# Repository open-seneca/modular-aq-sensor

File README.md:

| PCB version | Code version | Name | Pilot date | Lifecycle |
| :---: | :---: | :---: | :---: | :---: |
| v3 | v10 | Europe 21 | current | in production |
| v2 | v8/v9 | Kenya 20 | Mar-20 | in stock |
| v1 | v7 | Argentina 19 | May-19 | discontinued |
| v0 | v4 | CamBike sensor | Aug-18 | discontinued |

Please also refer to our current, smaller, and all-integrated air quality sensor kit which is also open-source on Github: 
https://github.com/open-seneca/integrated-aq-sensor

If you already have a sensor and want to upload and visualise your data you can create an account here:
http://app.open-seneca.org

If you have built your kit and want to flash the code to the Black Pill board, here is how:

a) Wiring and onboard jumpers:
- RX on the USB2TTL adapter to PA9, TX to PA10, GND to G, 3.3V to V3
- jumper B0+ to center pin, B1- to center pin

b) To flash the code:
- install Arduino Due in IDE board manager
- put Arduino_STM32 library (from the "hardware" folder in this repo) in "My Documents/Arduino/hardware" (Note: if the hardware folder doesn't exist you will need to create it)
- do the same for the content of the "library" folder in this repo
- start Arduino IDE and open the latest bp_vX from this repository
- under "Tools -> Board" select "Generic STM32F103C series"
- under "Tools -> Upload method" select Serial
- press reset button on the Black Pill to enter its flash mode
- click "Upload" to flash your code

c) To execute the code:
- after flashing code should run
- plug both header pins on low (B1- should be low already if your followed the steps correctly, move other jumper to B0-)
- the board will now keep its flash memory, every reset will restart execution

We are an open-source project, please feel free to extend and improve our code, just post a commit!

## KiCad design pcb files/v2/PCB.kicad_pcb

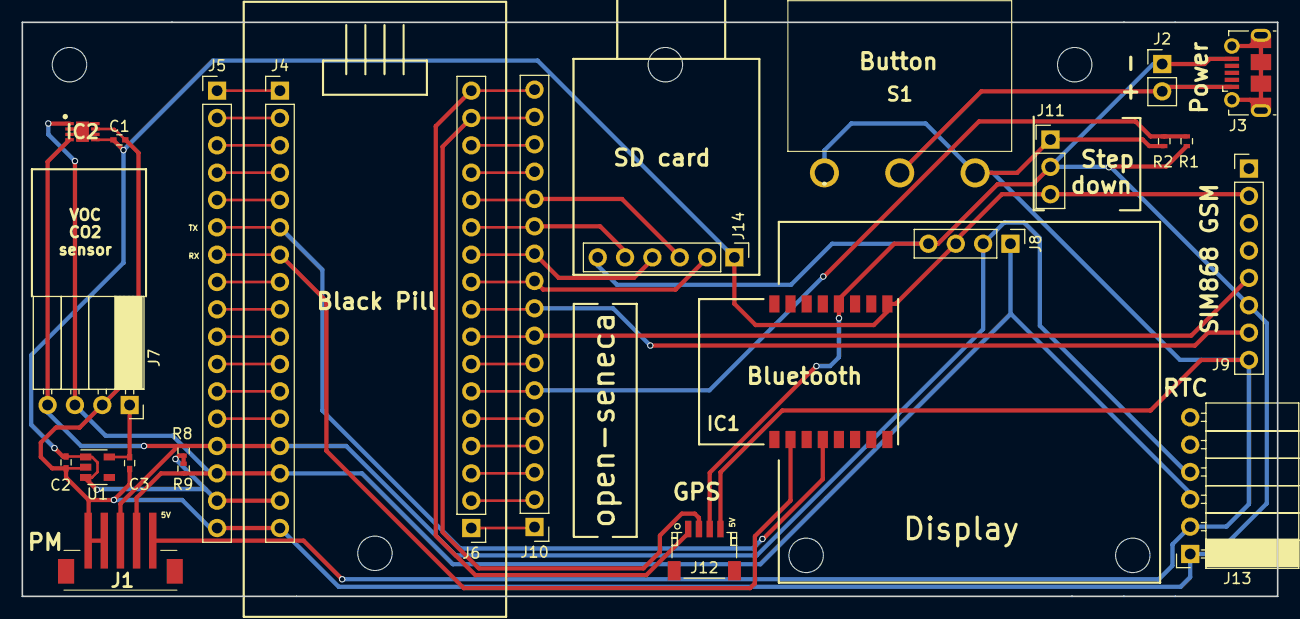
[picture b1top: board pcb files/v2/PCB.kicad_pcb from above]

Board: 2 copper layers, 116.6 x 53.3 mm, 31 parts (0 on the bottom side), 37 nets.

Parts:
C1: 100 nF; C_0402
C2, C3: 1 uF; C_0402
IC1: HM-11; HM-11-MODULE
IC2: SHT31-DIS-B; SON50P250X250X90-9N-D
J1: Conn_01x05; B5B-ZR-SM4-TF
J2: Conn_01x02; Pin_Header_Straight_1x02_Pitch2.54mm
J3: USB_OTG; USB_Micro-B_Molex-105017-0001
J4, J5, J6, J10: Conn_01x17; Socket_Strip_Straight_1x17_Pitch2.54mm
J7: Conn_01x04; Socket_Strip_Angled_1x04_Pitch2.54mm
J8: Conn_01x04; Socket_Strip_Straight_1x04_Pitch2.54mm
J9: Conn_01x08; Socket_Strip_Straight_1x08_Pitch2.54mm
J11: Conn_01x03; Socket_Strip_Straight_1x03_Pitch2.54mm
J12: Conn_01x04; JST_SH_SM04B-SRSS-TB_04x1.00mm_Angled
J13: Conn_01x06; Socket_Strip_Angled_1x06_Pitch2.54mm
J14: Conn_01x06; Socket_Strip_Straight_1x06_Pitch2.54mm
MK1, MK2, MK3, MK4, MK5, MK6: Mounting_Hole; MountingHole_3.2mm_M3
R1, R2, R8, R9: 4.7k; R_0402
S1: CWSA11AAN1H
U1: TLV70218_SOT23-5; SOT-23-5

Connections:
+3V3: C1.1, C2.1, IC1.9, IC2.5, J4.16, J5.16, J8.3, J9.2, J11.3, J14.1, R8.2, R9.2, U1.1, U1.3
+5V: J1.1, J9.8, J11.1, J12.4, J13.2, R2.1, S1.1, S1.3
/BT_RX: IC1.4, J4.6, J5.6
/BT_TX: IC1.2, J4.7, J5.7
/Bat: J6.6, J10.6, R1.1, R2.2
/Blue: J6.7, J10.7
/CStoSD: J6.10, J10.10, J14.2
/GPS_RX: J6.16, J10.16, J12.2
/GPS_TX: J6.17, J10.17, J12.1
/GSM_RX: J6.8, J9.5, J10.8
/GSM_TX: J6.9, J9.7, J10.9
/Green: J6.14, J10.14
/MISOtoSD: J6.12, J10.12, J14.5
/MOSItoSD: J6.13, J10.13, J14.3
/Red: J6.15, J10.15
/SCKtoSD: J6.11, J10.11, J14.4
/SCL: IC2.4, J1.3, J4.14, J5.14, J7.4, J8.2, J13.4, R8.1
/SDA: IC2.1, J1.2, J4.15, J5.15, J7.3, J8.1, J13.3, R9.1
GND: C1.2, C2.2, C3.2, IC1.12, IC2.2, IC2.7, IC2.8, IC2.9, J1.4, J1.5, J2.1, J3.5, J4.17, J5.17, J7.2, J8.4, J9.6, J11.2, J12.3, J13.1, J14.6, R1.2, U1.2
unnamed: C3.1, J7.1, U1.5
unnamed: J2.2, J3.1, S1.2
unnamed: J4.1, J5.1
unnamed: J4.2, J5.2
unnamed: J4.3, J5.3
unnamed: J4.4, J5.4
unnamed: J4.5, J5.5
unnamed: J4.8, J5.8
unnamed: J4.9, J5.9
unnamed: J4.10, J5.10
unnamed: J4.11, J5.11
unnamed: J4.12, J5.12
unnamed: J4.13, J5.13
unnamed: J6.1, J10.1
unnamed: J6.2, J10.2
unnamed: J6.3, J10.3
unnamed: J6.4, J10.4
unnamed: J6.5, J10.5

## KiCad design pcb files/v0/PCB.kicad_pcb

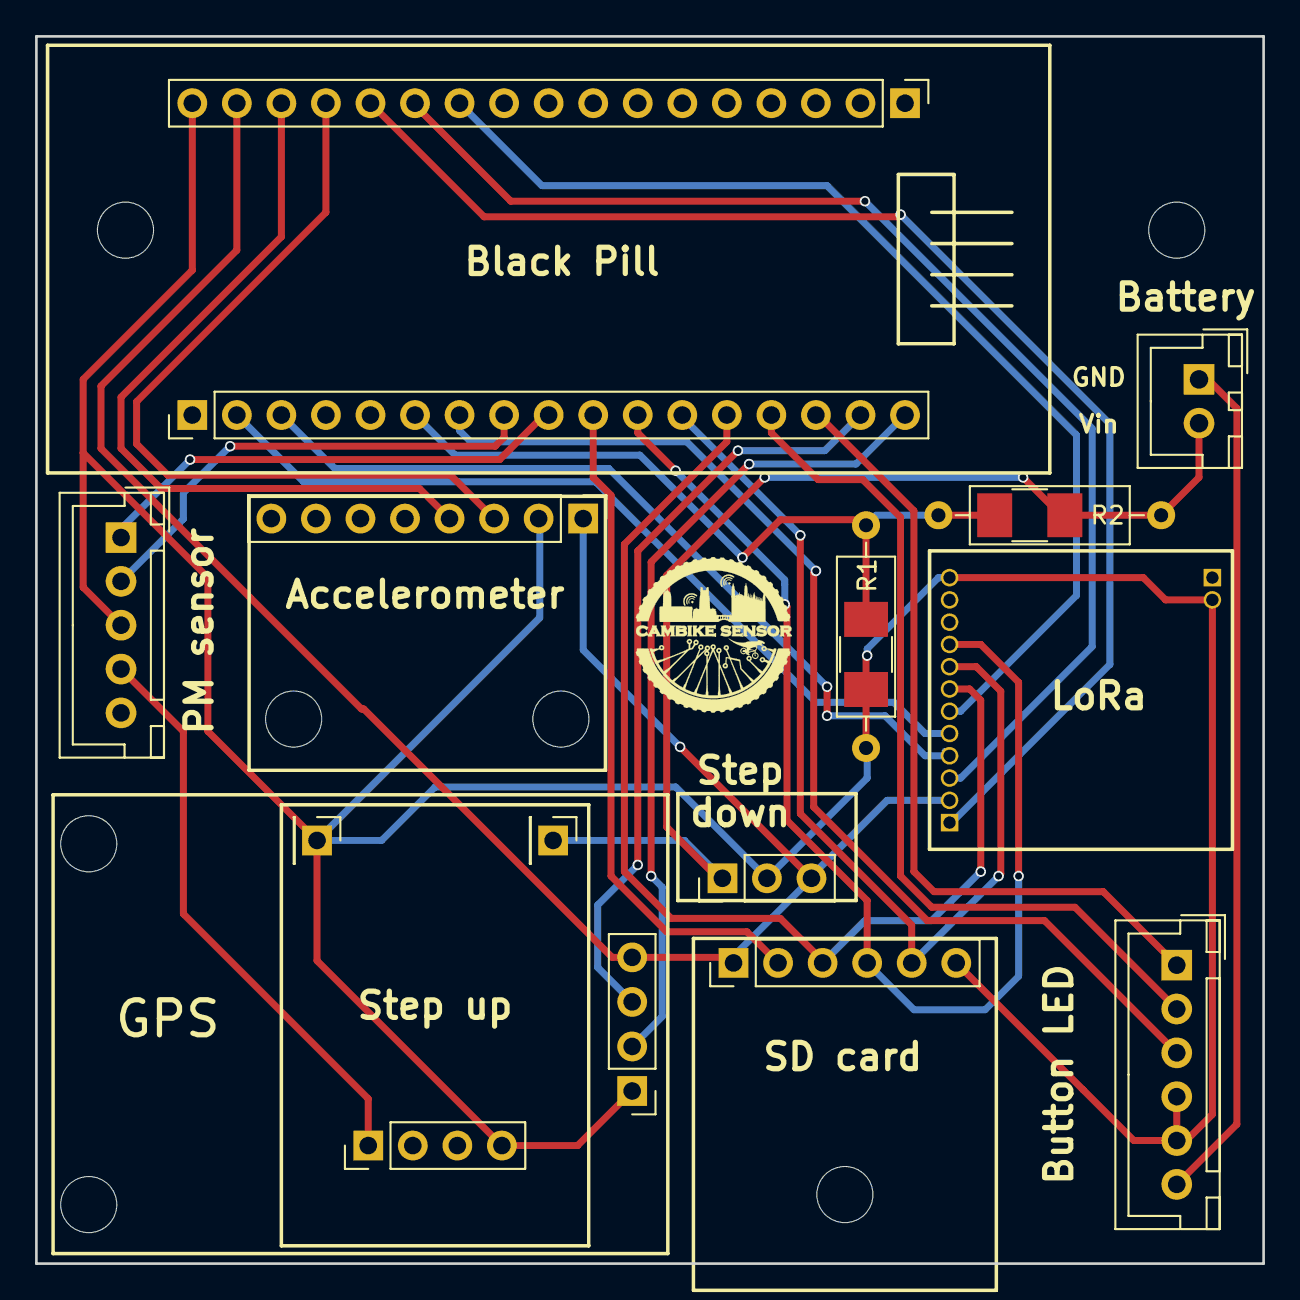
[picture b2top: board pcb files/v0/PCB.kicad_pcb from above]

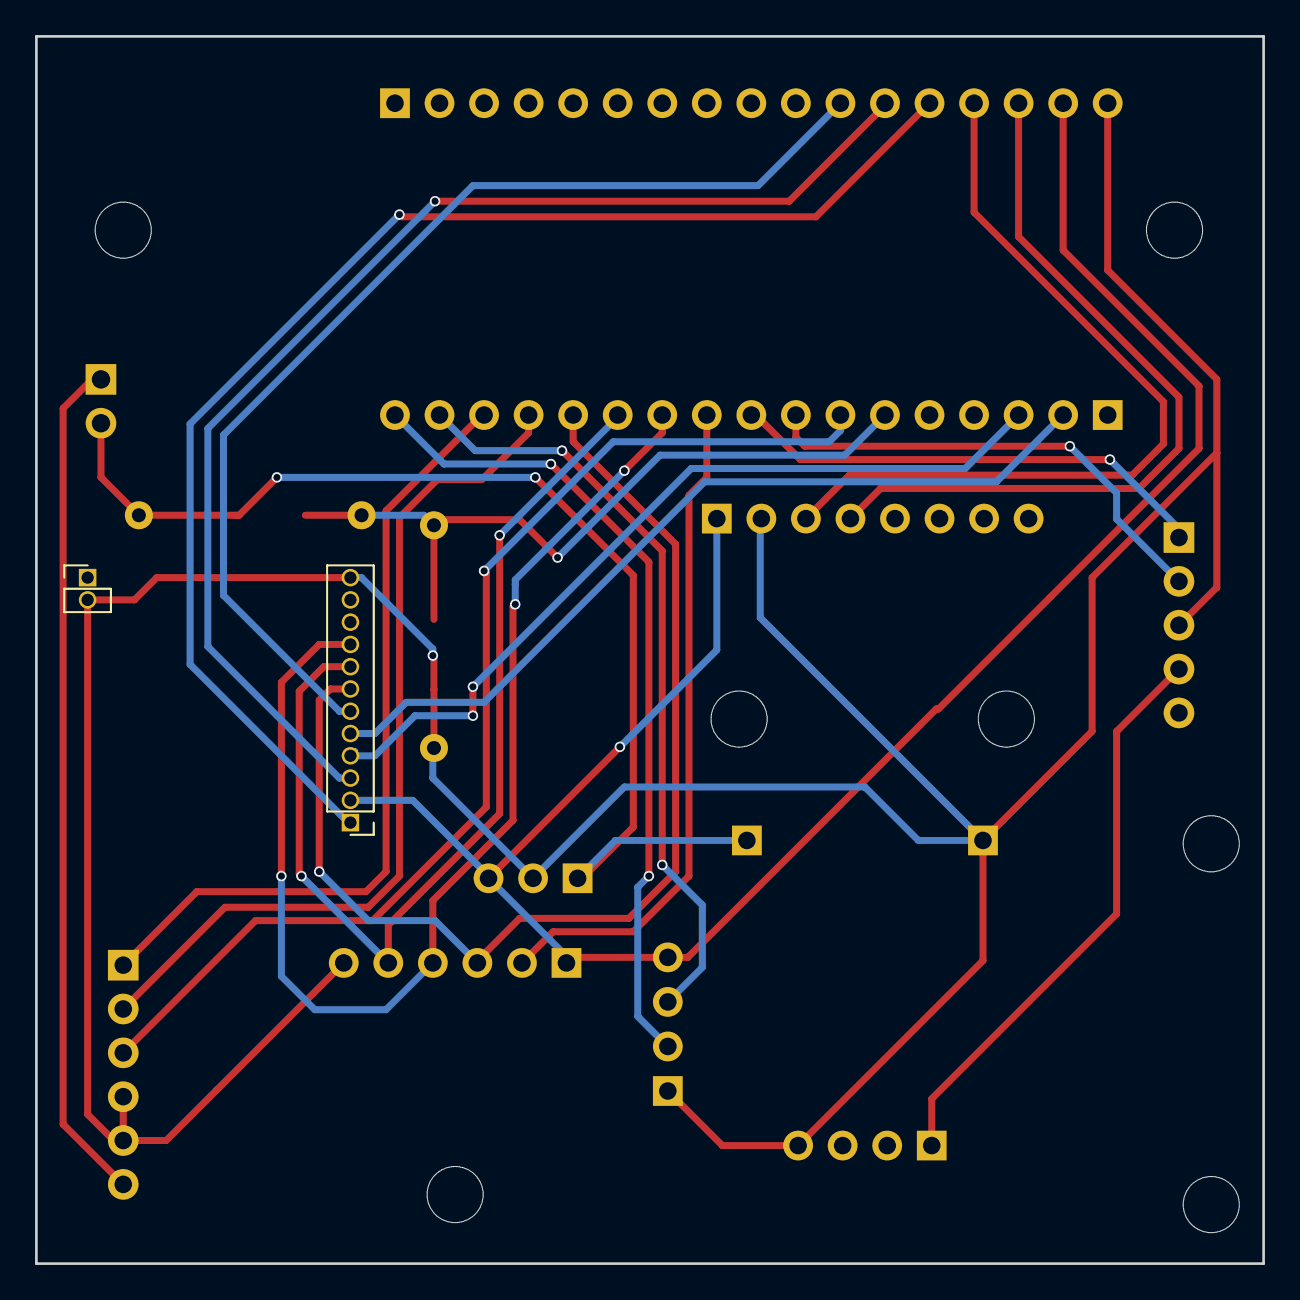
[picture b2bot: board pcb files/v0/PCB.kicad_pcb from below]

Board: 2 copper layers, 70.0 x 70.0 mm, 25 parts (2 on the bottom side), 24 nets.

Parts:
J1: Conn_01x08; Socket_Strip_Straight_1x08_Pitch2.54mm
J2: Conn_01x02; Socket_Strip_Straight_1x02_Pitch1.27mm
J3: Conn_01x12; Socket_Strip_Straight_1x12_Pitch1.27mm
J4: Conn_01x02; JST_XH_B02B-XH-A_02x2.50mm_Straight
J5, J10: Conn_01x17; Socket_Strip_Straight_1x17_Pitch2.54mm
J6, J7: Conn_01x01; Socket_Strip_Straight_1x01_Pitch2.54mm
J8: Conn_01x06; JST_XH_B06B-XH-A_06x2.50mm_Straight
J9, J12: Conn_01x04; Socket_Strip_Straight_1x04_Pitch2.54mm
J11: Conn_01x03; Socket_Strip_Straight_1x03_Pitch2.54mm
J13: Conn_01x05; JST_XH_B05B-XH-A_05x2.50mm_Straight
J14: Conn_01x06; Socket_Strip_Straight_1x06_Pitch2.54mm
MK1, MK2, MK3, MK4, MK5, MK6, MK7: Mounting_Hole; MountingHole_3.2mm_M3
R1, R2: 22k; R_1210_HandSoldering
R3, R4: 22k; R_Axial_DIN0309_L9.0mm_D3.2mm_P12.70mm_Horizontal

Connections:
+3V3: J1.1, J3.2, J5.16, J11.3, J12.4, J14.1
+5V: J9.1, J13.4
/Bat: J10.6, R1.1, R2.2, R3.1, R4.2
/Blue: J8.3, J10.7
/CS: J3.6, J5.11
/CStoSD: J10.10, J14.2
/DI0: J3.3, J5.12
/DI01: J3.4, J10.3
/DI02: J3.5, J10.2
/GPS_RX: J10.16, J12.3
/GPS_TX: J10.17, J12.2
/Green: J8.2, J10.14
/MISOtoSD: J3.8, J10.12, J14.5
/MOSItoSD: J3.7, J10.13, J14.3
/NO: J4.1, J8.6
/RESET: J3.1, J5.13
/RXtoSDS: J10.8, J13.2
/Red: J8.1, J10.15
/SCKtoSD: J3.9, J10.11, J14.4
/SCL: J1.3, J5.14
/SDA: J1.4, J5.15
/TXtoSDS: J10.9, J13.1
/Vin: J4.2, J6.1, J11.1, R2.1, R4.1
GND: J1.2, J2.2, J3.12, J5.17, J7.1, J8.4, J8.5, J9.4, J11.2, J12.1, J13.3, J14.6, R1.2, R3.2

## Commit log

2018-07-30 Readme updated
2018-07-30 Clean up
2018-08-01 Minor update
2018-08-02 Added battery status light
2018-08-15 Improved explanations
2018-08-15 Improvements
2018-08-27 PCB included
2018-08-30 Added laser cut case design file
2018-09-05 Cleanup and added casing files
2018-09-26 Updated assembly guide
2018-12-15 Added RGB LED button support
2019-03-16 Added bp_v5 (Kenya prototype)
2019-04-22 Code cleanup for ARG
2019-04-27 ARG update
2019-04-28 Fixed issues with v6
    GSM now more reliable
    CSV column order changed
2019-05-14 Updated documentation
2019-05-27 Added airflow model and PCB design
2019-08-12 v7 added
2019-09-09 Added v8 with VOC sensor support
2019-09-09 Fixing issue for VOC not plugged
2019-09-19 Gerber file v8
2019-09-19 Deleted unnecessary files
2019-09-19 Added PCB and pinout v8
2019-11-23 Added files for Nairobi distribution
2020-01-09 Add photo of functional board without the case
    SGP30 VOC sensor ordered from here: https://bit.ly/2ssk7yA
    Pins on SGP30 as delivered face in the opposite direction and so were
    desoldered and resoldered after 180 degrees rotation.
2020-01-12 Logo updated
2020-02-03 Updated cases for PCB v9
2020-02-03 Updated photo
2020-02-08 Wiki reactivated
2020-03-09 Added cowbell_v3
2020-03-11 Fixed error in v8 regarding file headers
2020-03-11 Fixed same error in v9
2020-03-18 Fixed minor issues in v8
2020-04-08 Print an error message when can't write to file
    If we can't write to the file to write the initial header than print out to the serial console to make the log output clearer.
2020-05-15 Shifted things around
2020-05-17 GPS fix in v9
2020-06-09 Fixed issue with SGP values becoming negative
2020-07-22 Added 3d printed airflow
2020-12-04 Cleanup and rearrangements
